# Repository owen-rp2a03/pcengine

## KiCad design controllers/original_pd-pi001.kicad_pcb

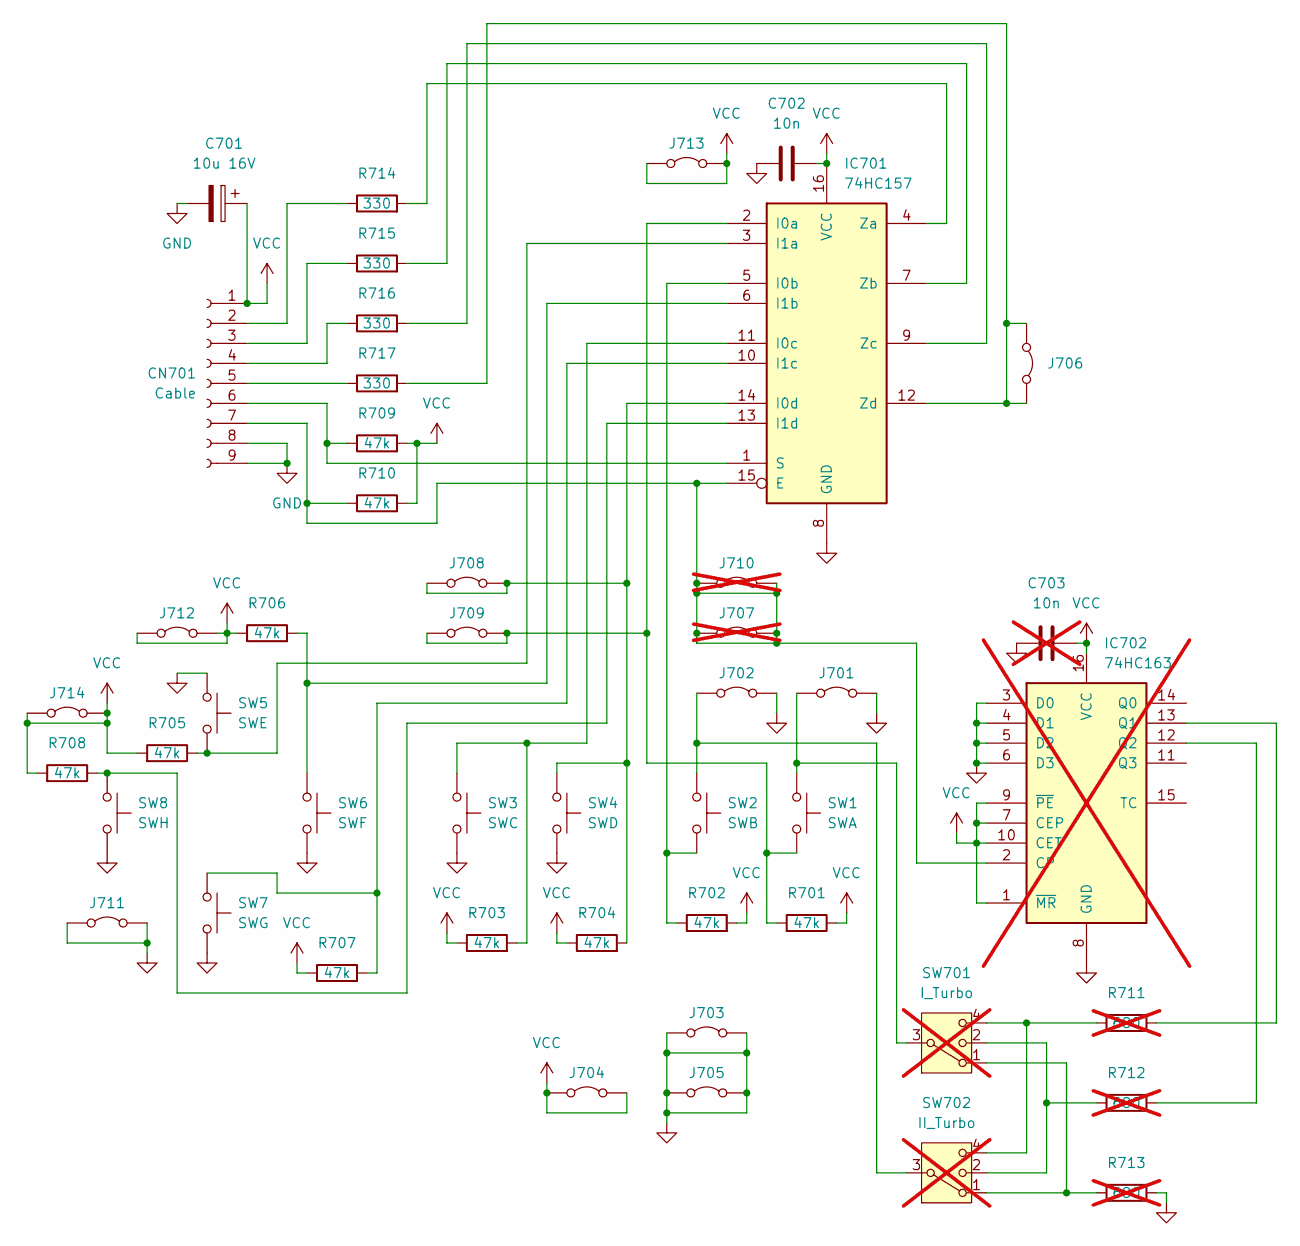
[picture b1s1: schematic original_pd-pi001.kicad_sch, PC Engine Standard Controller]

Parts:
C701: 10u 16V; CP_Controller_5.0mm
C702: 10n; C_Disc_Controller_5.0mm
C703: 10n; C_Disc_Controller_5.0mm; not fitted
CN701: Cable; JST_EH_S9B-EH_1x09_P2.50mm_Horizontal
IC701: 74HC157; DIP-16_W7.62mm_LongPads
IC702: 74HC163; DIP-16_W7.62mm_LongPads; not fitted
J701, J702: Jumper_2_Bridged; Jumper_Controller_Optional_7.5mm
J703, J704, J705, J706, J708, J709, J711, J712, J713, J714: Jumper_2_Bridged; Jumper_Controller_7.5mm
J707, J710: Jumper_2_Bridged; Jumper_Controller_7.5mm; not fitted
R701, R702, R703, R704, R705, R706, R707, R708, R709, R710: 47k; R_1206_3216Metric
R711, R712, R713: 680; R_1206_3216Metric; not fitted
R714, R715, R716, R717: 330; R_1206_3216Metric
SW1: SWA; SW_Controller_Pad_original
SW2: SWB; SW_Controller_Pad_original
SW3: SWC; SW_Controller_Pad_original
SW4: SWD; SW_Controller_Pad_original
SW5: SWE; SW_Controller_Pad_original
SW6: SWF; SW_Controller_Pad_original
SW7: SWG; SW_Controller_Pad_original
SW8: SWH; SW_Controller_Pad_original
SW701: I_Turbo; SW_Sliding_Surface_original; not fitted
SW702: II_Turbo; SW_Sliding_Surface_original; not fitted

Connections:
GND: C701.2, C702.2, C703.2, CN701.8, CN701.9, IC701.8 (GND), IC702.3 (D0), IC702.4 (D1), IC702.5 (D2), IC702.6 (D3), IC702.8 (GND), J701.1 (A), J702.2 (B), J703.1 (A), J703.2 (B), J705.1 (A), J705.2 (B), J711.1 (A), J711.2 (B), R713.1, SW3.2, SW4.2, SW5.1, SW6.2, SW7.2, SW8.2
unnamed: CN701.2, R714.1
unnamed: CN701.3, R715.1
unnamed: CN701.4, R716.1
unnamed: CN701.5, R717.1
unnamed: CN701.6, IC701.1 (S), R709.1
unnamed: CN701.7, IC701.15 (E), IC702.2 (CP), J707.1 (A), J707.2 (B), J710.1 (A), J710.2 (B), R710.1
unnamed: IC701.2 (I0a), J709.1 (A), J709.2 (B), R701.2, SW1.2
unnamed: IC701.5 (I0b), R702.1, SW2.2
unnamed: IC701.11 (I0c), R703.2, SW3.1
unnamed: IC701.14 (I0d), J708.1 (A), J708.2 (B), R704.2, SW4.1
unnamed: IC701.3 (I1a), R705.1, SW5.2
unnamed: IC701.6 (I1b), R706.2, SW6.1
unnamed: IC701.10 (I1c), R707.2, SW7.1
unnamed: IC701.13 (I1d), R708.1, SW8.1
unnamed: IC701.4 (Za), R714.2
unnamed: IC701.7 (Zb), R715.2
unnamed: IC701.9 (Zc), R716.2
unnamed: IC701.12 (Zd), J706.1 (A), J706.2 (B), R717.2
unnamed: IC702.13 (Q1), R711.1
unnamed: IC702.12 (Q2), R712.2
unnamed: J701.2 (B), SW1.1, SW701.3
unnamed: J702.1 (A), SW2.1, SW702.3
unnamed: R711.2, SW701.4, SW702.4
unnamed: R712.1, SW701.2, SW702.2
unnamed: R713.2, SW701.1, SW702.1
VCC: C701.1, C702.1, C703.1, CN701.1, IC701.16 (VCC), IC702.1 (~MR), IC702.7 (CEP), IC702.9 (~PE), IC702.10 (CET), IC702.16 (VCC), J704.1 (A), J704.2 (B), J712.1 (A), J712.2 (B), J713.1 (A), J713.2 (B), J714.1 (A), J714.2 (B), R701.1, R702.2, R703.1, R704.1, R705.2, R706.1, R707.1, R708.2, R709.2, R710.2

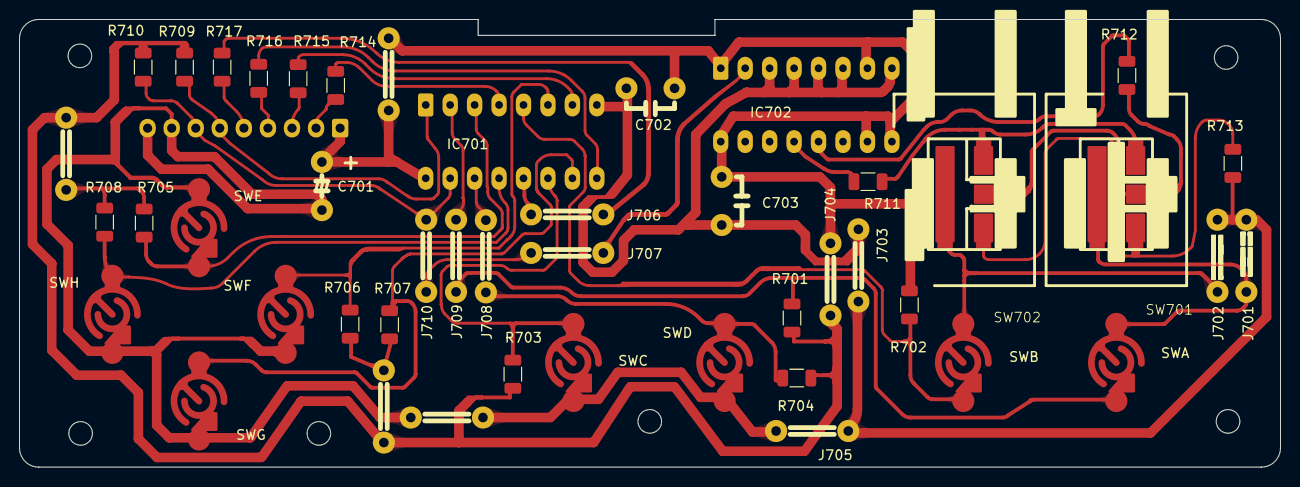
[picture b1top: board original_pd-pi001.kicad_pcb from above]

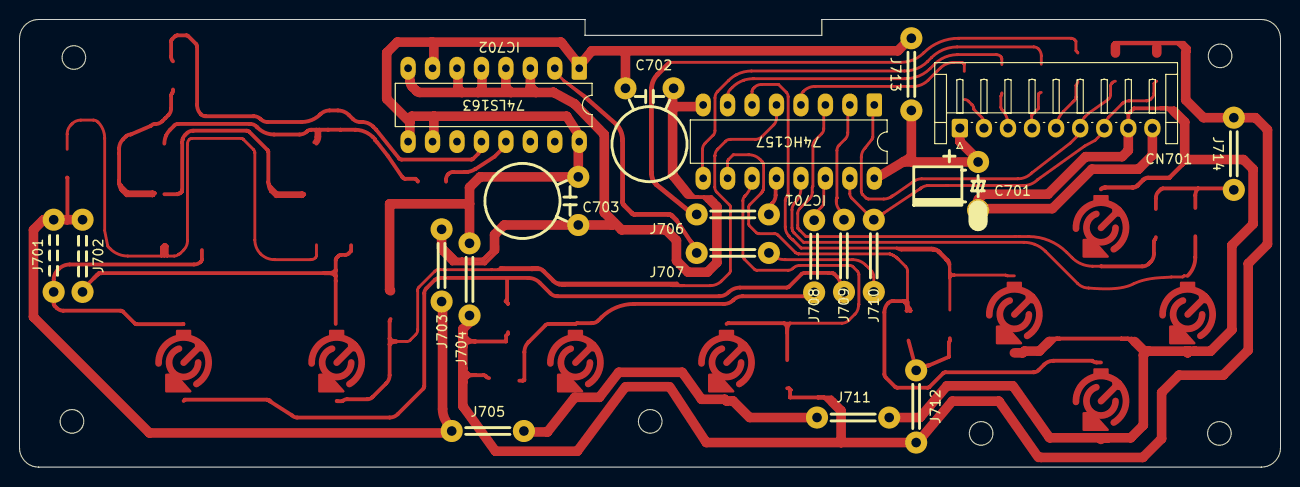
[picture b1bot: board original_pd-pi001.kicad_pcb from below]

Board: 2 copper layers, 131.0 x 46.5 mm, 47 parts (20 on the bottom side), 27 nets.
